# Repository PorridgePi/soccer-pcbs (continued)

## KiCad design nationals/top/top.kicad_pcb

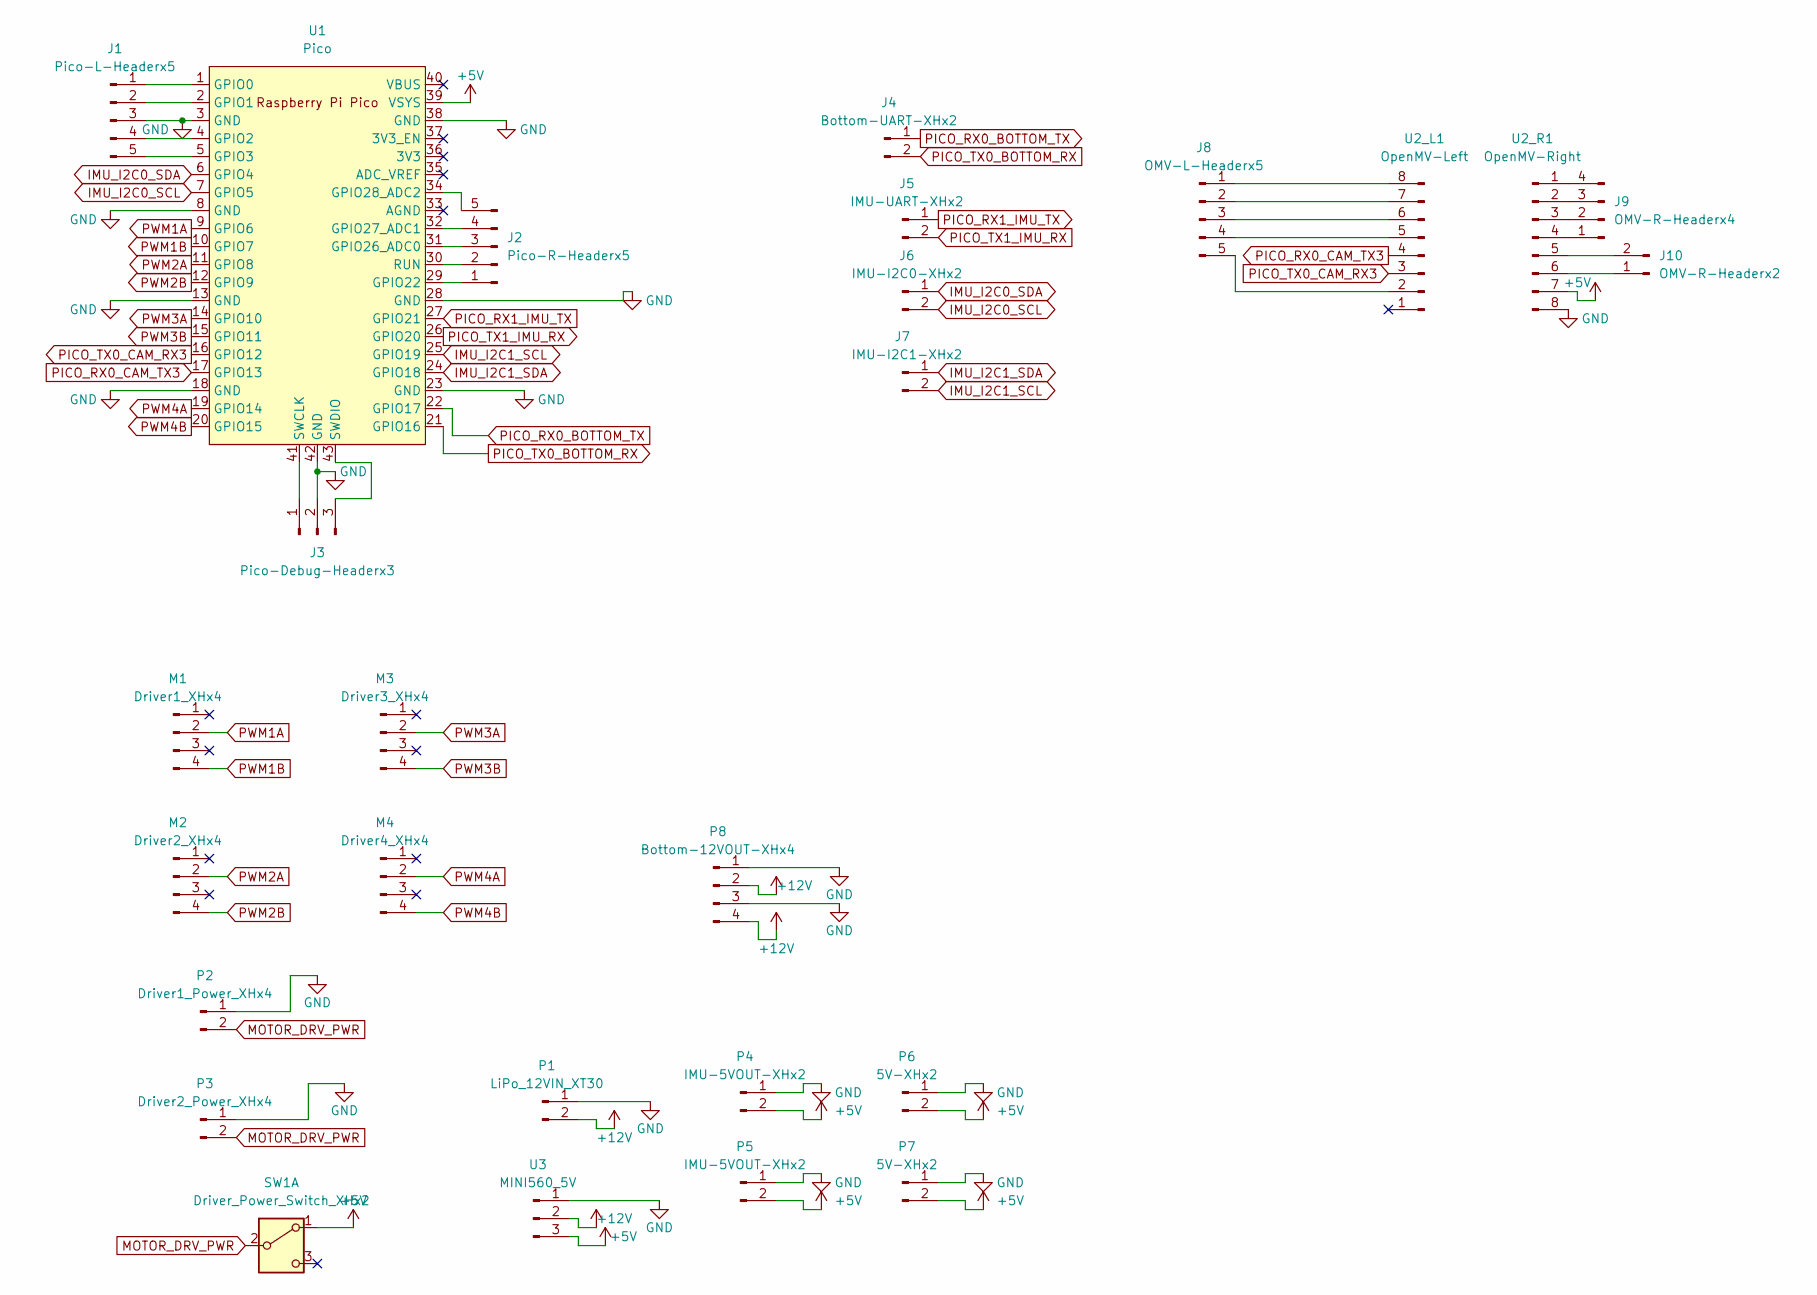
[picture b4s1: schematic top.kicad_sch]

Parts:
J1: Pico-L-Headerx5; PinHeader_1x05_P2.54mm_Vertical
J2: Pico-R-Headerx5; PinHeader_1x05_P2.54mm_Vertical
J3: Pico-Debug-Headerx3; PinHeader_1x03_P2.54mm_Vertical
J4: Bottom-UART-XHx2; JST_XH_B2B-XH-A_1x02_P2.50mm_Vertical
J5: IMU-UART-XHx2; JST_XH_B2B-XH-A_1x02_P2.50mm_Vertical
J6: IMU-I2C0-XHx2; JST_XH_B2B-XH-A_1x02_P2.50mm_Vertical
J7: IMU-I2C1-XHx2; JST_XH_B2B-XH-A_1x02_P2.50mm_Vertical
J8: OMV-L-Headerx5; PinHeader_1x05_P2.54mm_Vertical
J9: OMV-R-Headerx4; PinSocket_1x04_P2.54mm_Vertical
J10: OMV-R-Headerx2; PinHeader_1x02_P2.54mm_Vertical
M1: Driver1_XHx4; JST_XH_B4B-XH-A_1x04_P2.50mm_Vertical
M2: Driver2_XHx4; JST_XH_B4B-XH-A_1x04_P2.50mm_Vertical
M3: Driver3_XHx4; JST_XH_B4B-XH-A_1x04_P2.50mm_Vertical
M4: Driver4_XHx4; JST_XH_B4B-XH-A_1x04_P2.50mm_Vertical
P1: LiPo_12VIN_XT30; AMASS_XT30PW-F_1x02_P2.50mm_Horizontal
P2: Driver1_Power_XHx4; JST_XH_B2B-XH-A_1x02_P2.50mm_Vertical
P3: Driver2_Power_XHx4; JST_XH_B2B-XH-A_1x02_P2.50mm_Vertical
P4, P5: IMU-5VOUT-XHx2; JST_XH_B2B-XH-A_1x02_P2.50mm_Vertical
P6, P7: 5V-XHx2; JST_XH_B2B-XH-A_1x02_P2.50mm_Vertical
P8: Bottom-12VOUT-XHx4; JST_XH_B4B-XH-A_1x04_P2.50mm_Vertical
SW1: Driver_Power_Switch_XHx2; JST_XH_B2B-XH-A_1x02_P2.50mm_Vertical
U1: Pico; Raspberry_Pi_Pico_SMT_THT
U2_L1: OpenMV-Left; PinHeader_1x08_P2.54mm_Vertical
U2_R1: OpenMV-Right; PinHeader_1x08_P2.54mm_Vertical
U3: MINI560_5V; MINI560

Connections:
+5V: P4.2, P5.2, P6.2, P7.2, SW1.1 (A), U1.39 (VSYS), U2_R1.7, U3.3
+12V: P1.2, P8.2, P8.4, U3.2
GND: J1.3, J3.2, P1.1, P2.1, P3.1, P4.1, P5.1, P6.1, P7.1, P8.1, P8.3, U1.3 (GND), U1.8 (GND), U1.13 (GND), U1.18 (GND), U1.23 (GND), U1.28 (GND), U1.38 (GND), U1.42 (GND), U2_R1.8, U3.1
IMU_I2C0_SCL: J6.2, U1.7 (GPIO5)
IMU_I2C0_SDA: J6.1, U1.6 (GPIO4)
IMU_I2C1_SCL: J7.2, U1.25 (GPIO19)
IMU_I2C1_SDA: J7.1, U1.24 (GPIO18)
MOTOR_DRV_PWR: P2.2, P3.2, SW1.2 (B)
unnamed: J1.1, U1.1 (GPIO0)
unnamed: J1.2, U1.2 (GPIO1)
unnamed: J1.4, U1.4 (GPIO2)
unnamed: J1.5, U1.5 (GPIO3)
unnamed: J2.1, U1.29 (GPIO22)
unnamed: J2.2, U1.30 (RUN)
unnamed: J2.3, U1.31 (GPIO26_ADC0)
unnamed: J2.4, U1.32 (GPIO27_ADC1)
unnamed: J2.5, U1.34 (GPIO28_ADC2)
unnamed: J3.1, U1.41 (SWCLK)
unnamed: J3.3, U1.43 (SWDIO)
unnamed: J8.1, U2_L1.8
unnamed: J8.2, U2_L1.7
unnamed: J8.3, U2_L1.6
unnamed: J8.4, U2_L1.5
unnamed: J8.5, U2_L1.2
unnamed: J9.1, U2_R1.4
unnamed: J9.2, U2_R1.3
unnamed: J9.3, U2_R1.2
unnamed: J9.4, U2_R1.1
unnamed: J10.1, U2_R1.6
unnamed: J10.2, U2_R1.5
PICO_RX0_BOTTOM_TX: J4.1, U1.22 (GPIO17)
PICO_RX0_CAM_TX3: U1.17 (GPIO13), U2_L1.4
PICO_RX1_IMU_TX: J5.1, U1.27 (GPIO21)
PICO_TX0_BOTTOM_RX: J4.2, U1.21 (GPIO16)
PICO_TX0_CAM_RX3: U1.16 (GPIO12), U2_L1.3
PICO_TX1_IMU_RX: J5.2, U1.26 (GPIO20)
PWM1A: M1.2, U1.9 (GPIO6)
PWM1B: M1.4, U1.10 (GPIO7)
PWM2A: M2.2, U1.11 (GPIO8)
PWM2B: M2.4, U1.12 (GPIO9)
PWM3A: M3.2, U1.14 (GPIO10)
PWM3B: M3.4, U1.15 (GPIO11)
PWM4A: M4.2, U1.19 (GPIO14)
PWM4B: M4.4, U1.20 (GPIO15)

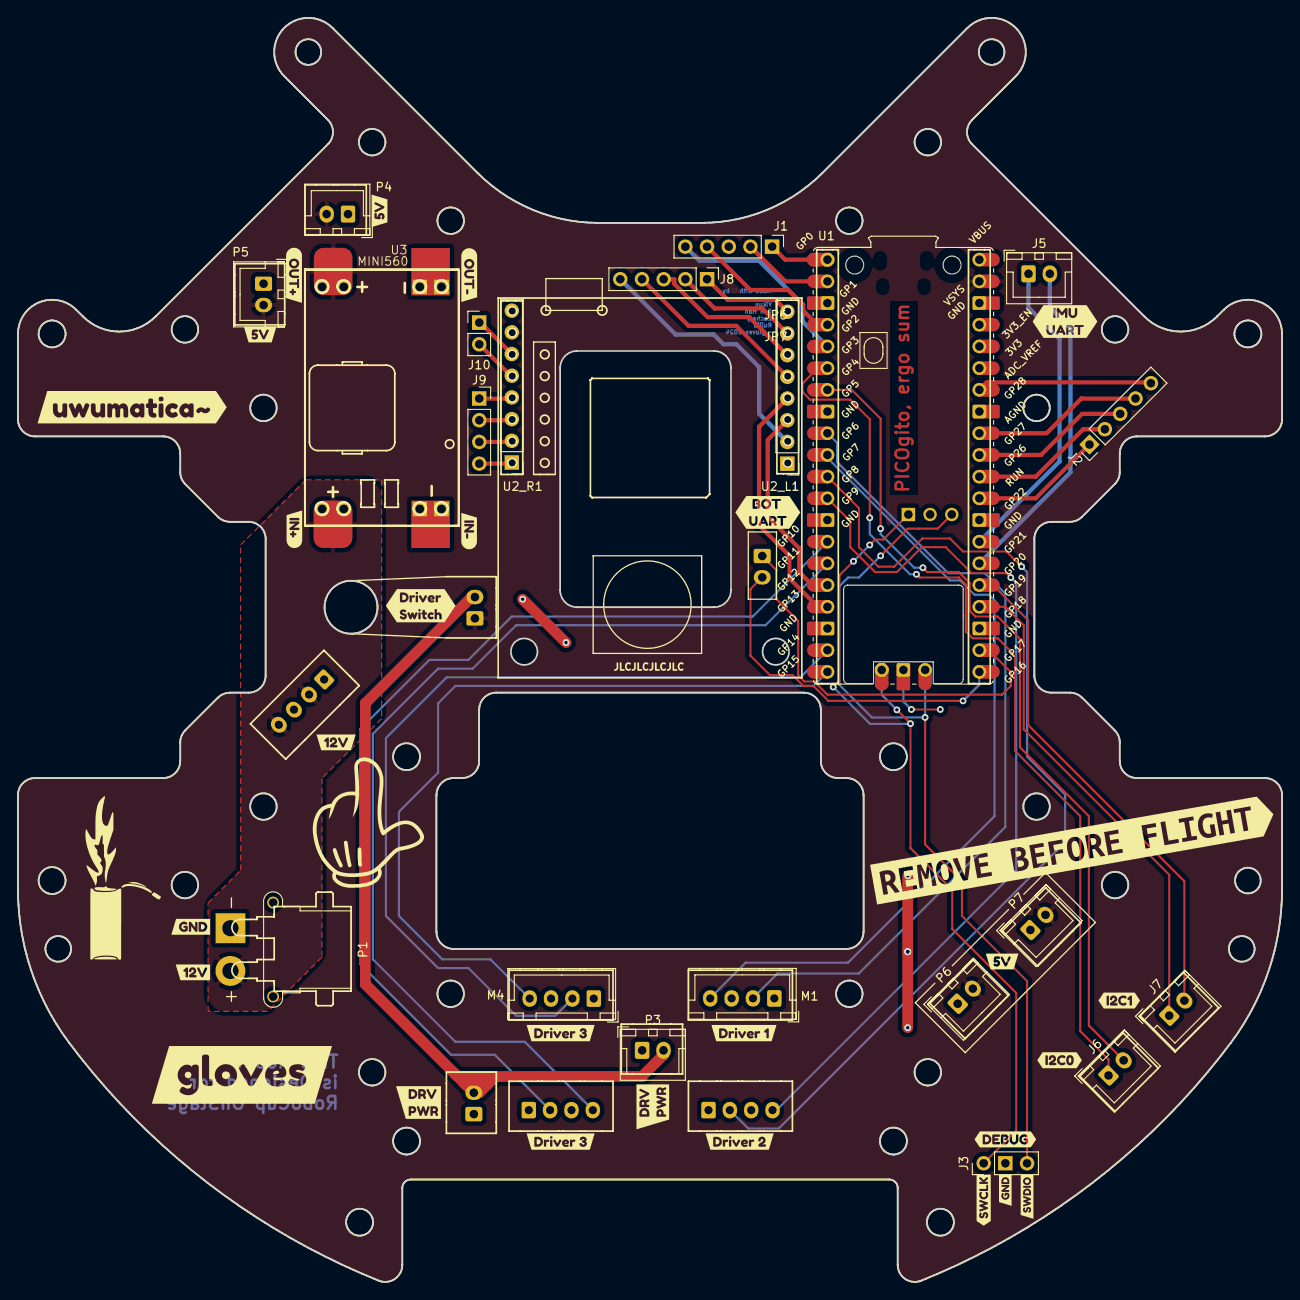
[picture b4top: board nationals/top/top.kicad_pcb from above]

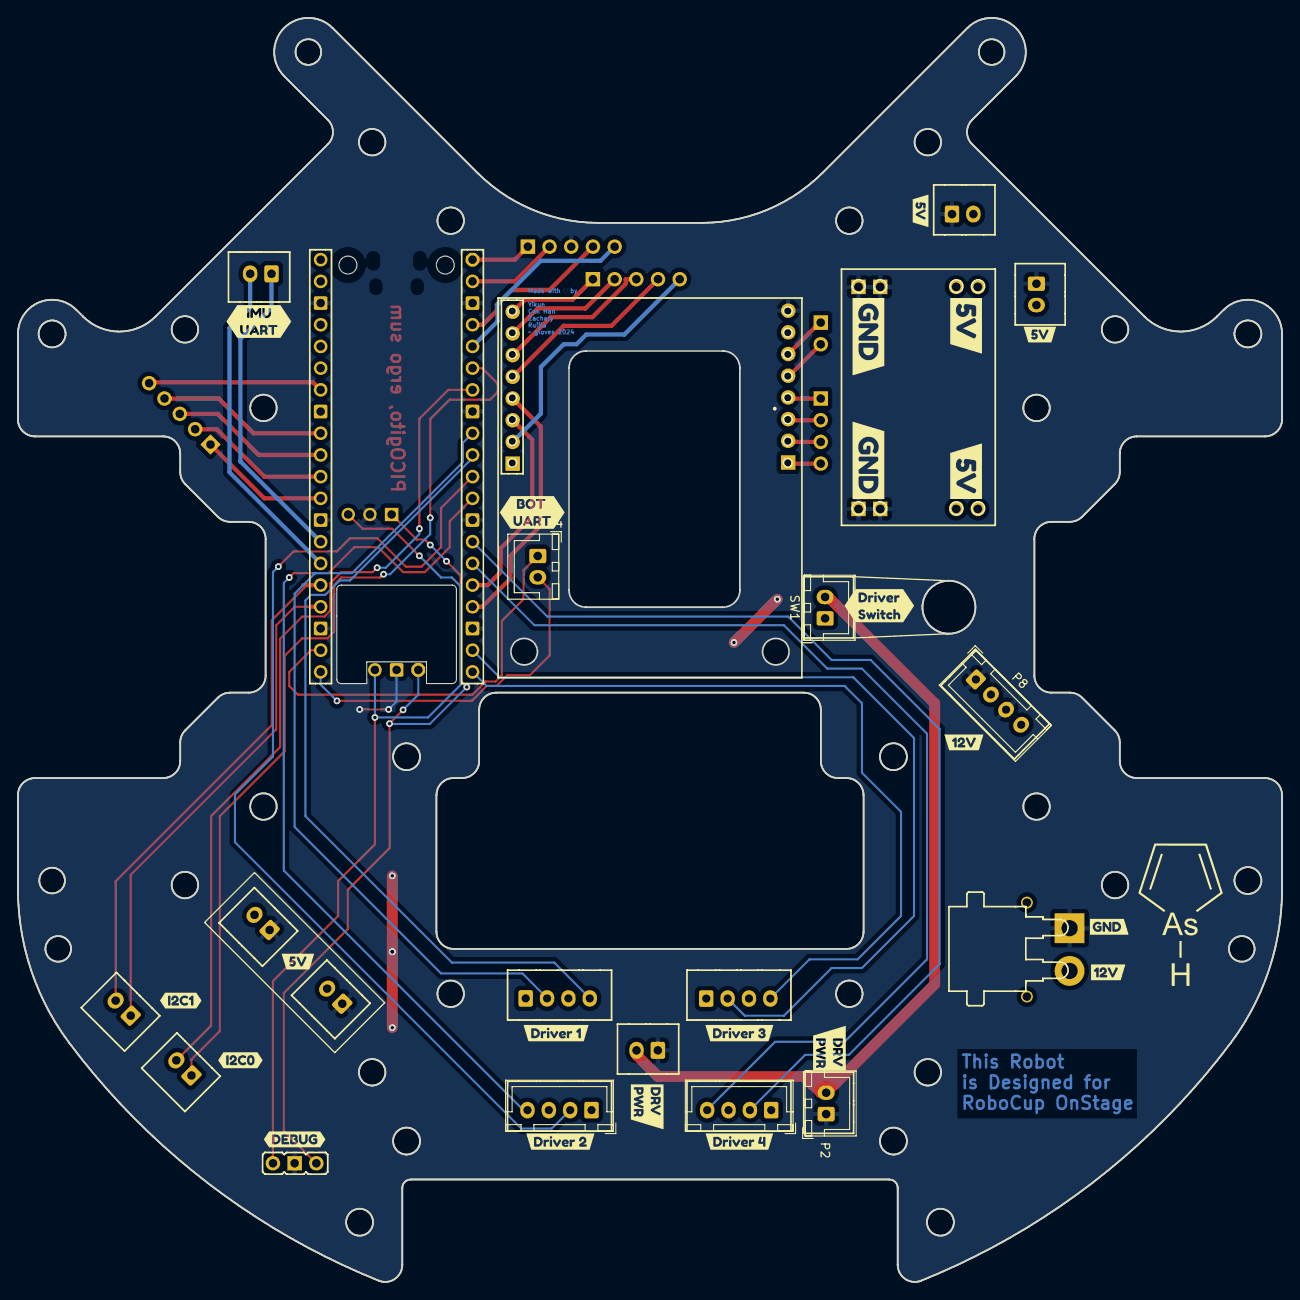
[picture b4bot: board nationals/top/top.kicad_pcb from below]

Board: 2 copper layers, 148.0 x 148.0 mm, 73 parts (28 on the bottom side), 44 nets.

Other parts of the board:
kibuzzard-65B87A32, kibuzzard-65B87A32#2, kibuzzard-65B87A32#3, kibuzzard-65B87A32#4, kibuzzard-65B87A32#5, kibuzzard-65B87A32#6: G***; kibuzzard-65B87A32
kibuzzard-65B87C2D: G***; kibuzzard-65B87C2D
kibuzzard-65B87C4C: G***; kibuzzard-65B87C4C
kibuzzard-65B87C77: G***; kibuzzard-65B87C77
kibuzzard-65B87C82: G***; kibuzzard-65B87C82
kibuzzard-65B87CF7, kibuzzard-65B87CF7#2: G***; kibuzzard-65B87CF7
kibuzzard-65B87D10, kibuzzard-65B87D10#2: G***; kibuzzard-65B87D10
kibuzzard-65B89F23: G***; kibuzzard-65B89F23
kibuzzard-65B872C5, kibuzzard-65B872C5#2, kibuzzard-65B872C5#3: G***; kibuzzard-65B872C5
kibuzzard-65B872D0: G***; kibuzzard-65B872D0
kibuzzard-65B874B6, kibuzzard-65B874B6#2: G***; kibuzzard-65B874B6
kibuzzard-65B876C6: G***; kibuzzard-65B876C6
kibuzzard-65B877B7, kibuzzard-65B877B7#2, kibuzzard-65B877B7#3: G***; kibuzzard-65B877B7
kibuzzard-65B878F9, kibuzzard-65B878F9#2: G***; kibuzzard-65B878F9
kibuzzard-65B8729F, kibuzzard-65B8729F#2: G***; kibuzzard-65B8729F
kibuzzard-65B8733B, kibuzzard-65B8733B#2: G***; kibuzzard-65B8733B
kibuzzard-65B8746C: G***; kibuzzard-65B8746C
kibuzzard-65B8747C: G***; kibuzzard-65B8747C
kibuzzard-65B8749D: G***; kibuzzard-65B8749D
kibuzzard-65B8779B: G***; kibuzzard-65B8779B
kibuzzard-65B8902F: G***; kibuzzard-65B8902F
kibuzzard-65B87292, kibuzzard-65B87292#2: G***; kibuzzard-65B87292
kibuzzard-65B87357, kibuzzard-65B87357#2: G***; kibuzzard-65B87357
kibuzzard-65B87709: G***; kibuzzard-65B87709
kibuzzard-65B87723: G***; kibuzzard-65B87723
kibuzzard-65B87731: G***; kibuzzard-65B87731
kibuzzard-65B87948, kibuzzard-65B87948#2: G***; kibuzzard-65B87948
kibuzzard-65B89082: G***; kibuzzard-65B89082

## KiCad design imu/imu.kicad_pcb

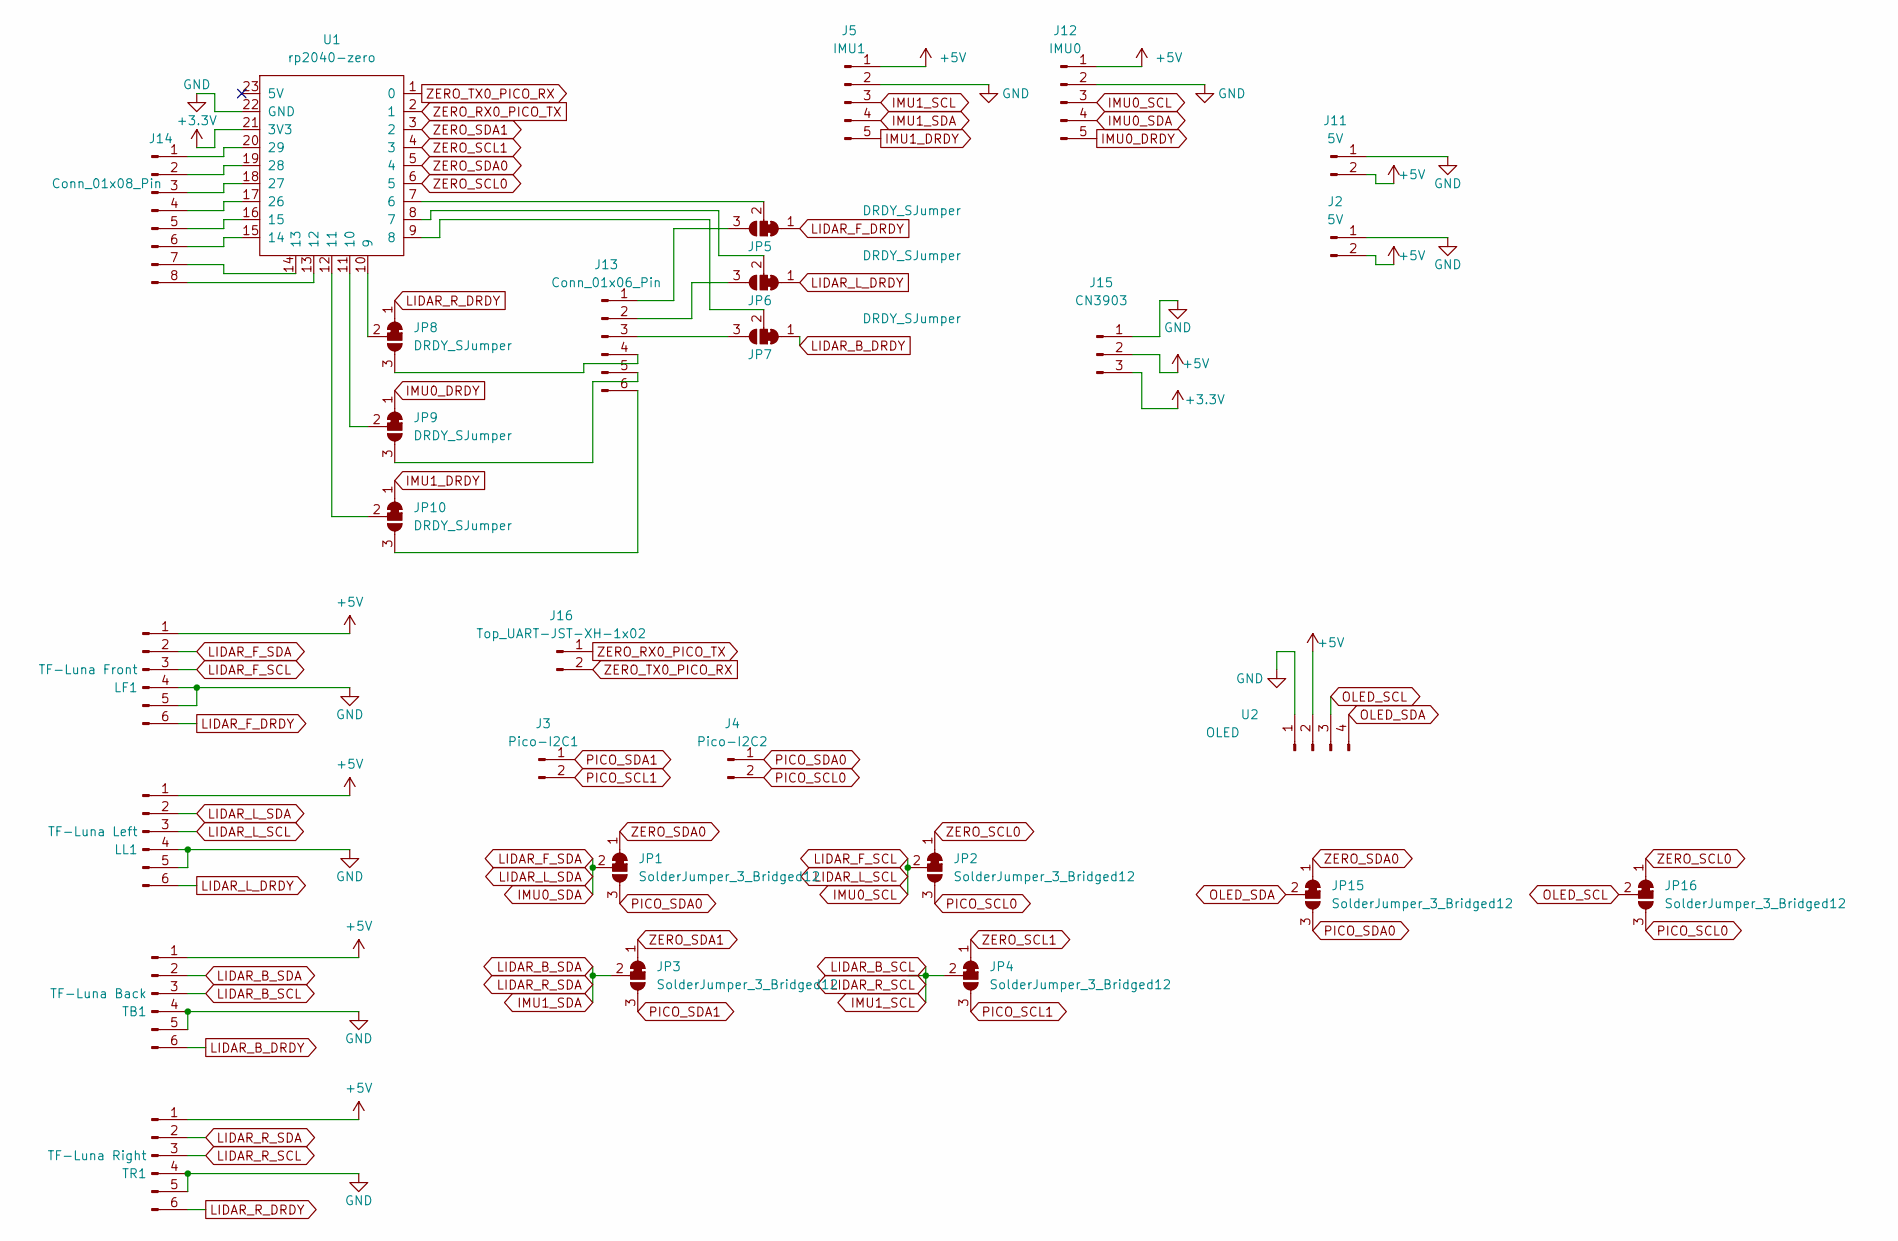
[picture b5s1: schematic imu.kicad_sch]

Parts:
J2, J11: 5V; JST_XH_B2B-XH-A_1x02_P2.50mm_Vertical
J3: Pico-I2C1; JST_XH_B2B-XH-A_1x02_P2.50mm_Vertical
J4: Pico-I2C2; JST_XH_B2B-XH-A_1x02_P2.50mm_Vertical
J5: IMU1; JST_XH_B5B-XH-A_1x05_P2.50mm_Vertical
J12: IMU0; JST_XH_B5B-XH-A_1x05_P2.50mm_Vertical
J13: Conn_01x06_Pin; PinHeader_1x06_P2.54mm_Vertical
J14: Conn_01x08_Pin; PinHeader_1x08_P2.54mm_Vertical
J15: CN3903
J16: Top_UART-JST-XH-1x02; JST_XH_B2B-XH-A_1x02_P2.50mm_Vertical
JP1, JP2, JP3, JP4, JP15, JP16: SolderJumper_3_Bridged12; SolderJumper-3_P1.3mm_Bridged2Bar12_RoundedPad1.0x1.5mm_Num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
JP5, JP6, JP7, JP8, JP9, JP10: DRDY_SJumper; SolderJumper-3_P1.3mm_Bridged2Bar12_RoundedPad1.0x1.5mm_Num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
LF1: TF-Luna Front; JST_XH_B6B-XH-A_1x06_P2.50mm_Vertical
LL1: TF-Luna Left; JST_XH_B6B-XH-A_1x06_P2.50mm_Vertical
TB1: TF-Luna Back; JST_XH_B6B-XH-A_1x06_P2.50mm_Vertical
TR1: TF-Luna Right; JST_XH_B6B-XH-A_1x06_P2.50mm_Vertical
U1: rp2040-zero; rp2040-zero-tht-pads
U2: OLED; PinHeader_1x04_P2.54mm_Vertical

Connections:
+3.3V: J15.3, U1.21 (3V3)
+5V: J2.2, J5.1, J11.2, J12.1, J15.2, LF1.1, LL1.1, TB1.1, TR1.1, U2.2
GND: J2.1, J5.2, J11.1, J12.2, J15.1, LF1.4, LF1.5, LL1.4, LL1.5, TB1.4, TB1.5, TR1.4, TR1.5, U1.22 (GND), U2.1
IMU0_DRDY: J12.5, JP9.1 (A)
IMU0_SCL: J12.3, JP2.2 (C), LF1.3, LL1.3
IMU0_SDA: J12.4, JP1.2 (C), LF1.2, LL1.2
IMU1_DRDY: J5.5, JP10.1 (A)
IMU1_SCL: J5.3, JP4.2 (C), TB1.3, TR1.3
IMU1_SDA: J5.4, JP3.2 (C), TB1.2, TR1.2
LIDAR_B_DRDY: JP7.1 (A), TB1.6
LIDAR_F_DRDY: JP5.1 (A), LF1.6
LIDAR_L_DRDY: JP6.1 (A), LL1.6
LIDAR_R_DRDY: JP8.1 (A), TR1.6
unnamed: J13.1, JP5.3 (B)
unnamed: J13.2, JP6.3 (B)
unnamed: J13.3, JP7.3 (B)
unnamed: J13.4, JP8.3 (B)
unnamed: J13.5, JP9.3 (B)
unnamed: J13.6, JP10.3 (B)
unnamed: J14.1, U1.20 (29)
unnamed: J14.2, U1.19 (28)
unnamed: J14.3, U1.18 (27)
unnamed: J14.4, U1.17 (26)
unnamed: J14.5, U1.16 (15)
unnamed: J14.6, U1.15 (14)
unnamed: J14.7, U1.14 (13)
unnamed: J14.8, U1.13 (12)
unnamed: JP5.2 (C), U1.7 (6)
unnamed: JP6.2 (C), U1.8 (7)
unnamed: JP7.2 (C), U1.9 (8)
unnamed: JP8.2 (C), U1.10 (9)
unnamed: JP9.2 (C), U1.11 (10)
unnamed: JP10.2 (C), U1.12 (11)
OLED_SCL: JP16.2 (C), U2.3
OLED_SDA: JP15.2 (C), U2.4
PICO_SCL0: J4.2, JP2.3 (B), JP16.3 (B)
PICO_SCL1: J3.2, JP4.3 (B)
PICO_SDA0: J4.1, JP1.3 (B), JP15.3 (B)
PICO_SDA1: J3.1, JP3.3 (B)
ZERO_RX0_PICO_TX: J16.1, U1.2 (1)
ZERO_SCL0: JP2.1 (A), JP16.1 (A), U1.6 (5)
ZERO_SCL1: JP4.1 (A), U1.4 (3)
ZERO_SDA0: JP1.1 (A), JP15.1 (A), U1.5 (4)
ZERO_SDA1: JP3.1 (A), U1.3 (2)
ZERO_TX0_PICO_RX: J16.2, U1.1 (0)

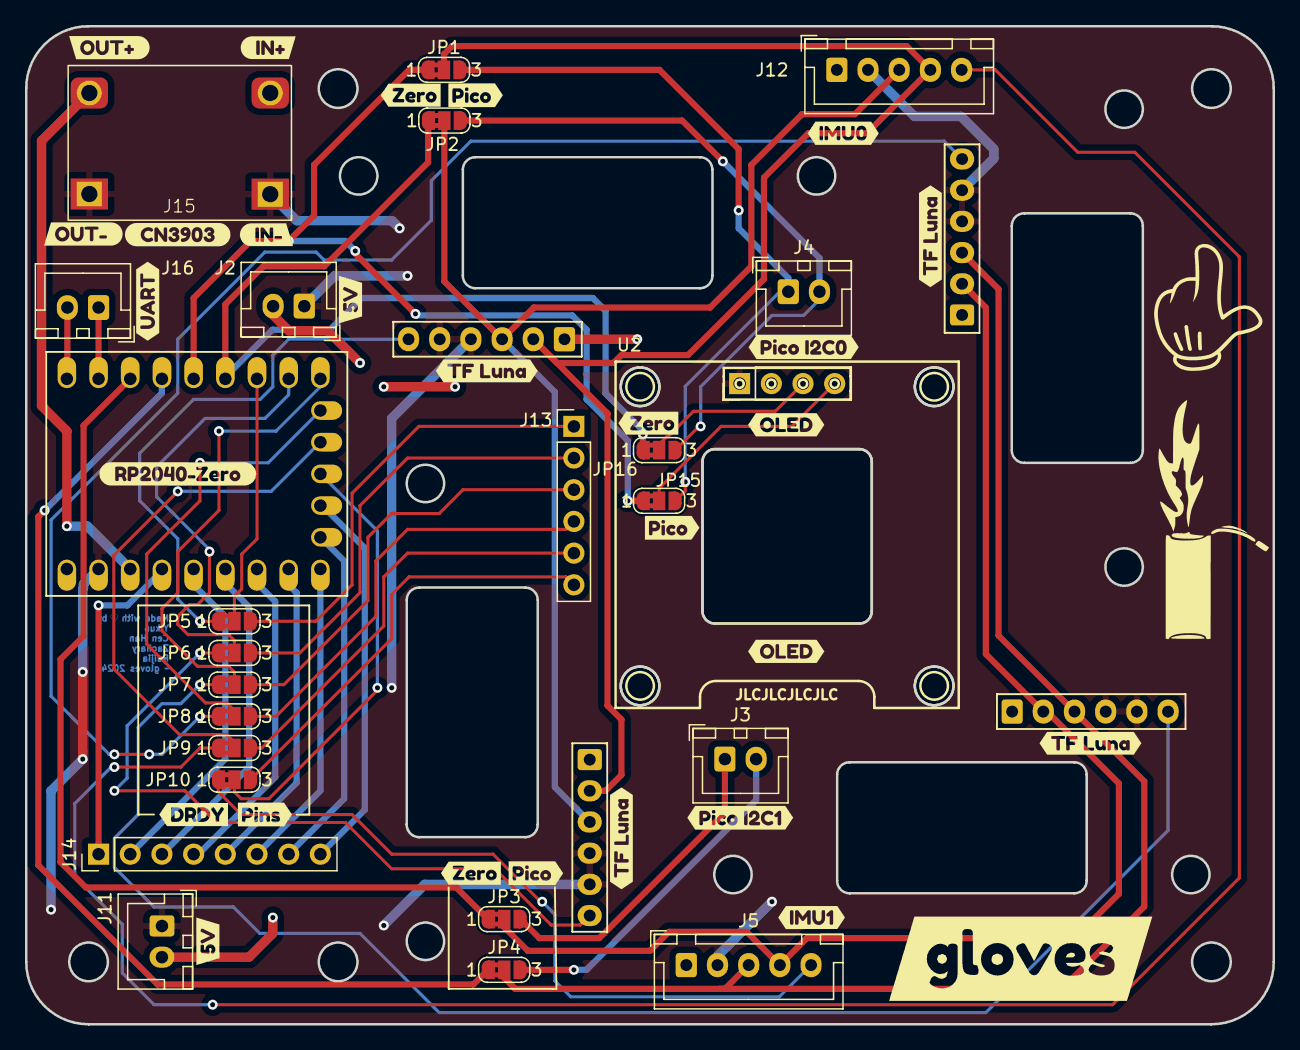
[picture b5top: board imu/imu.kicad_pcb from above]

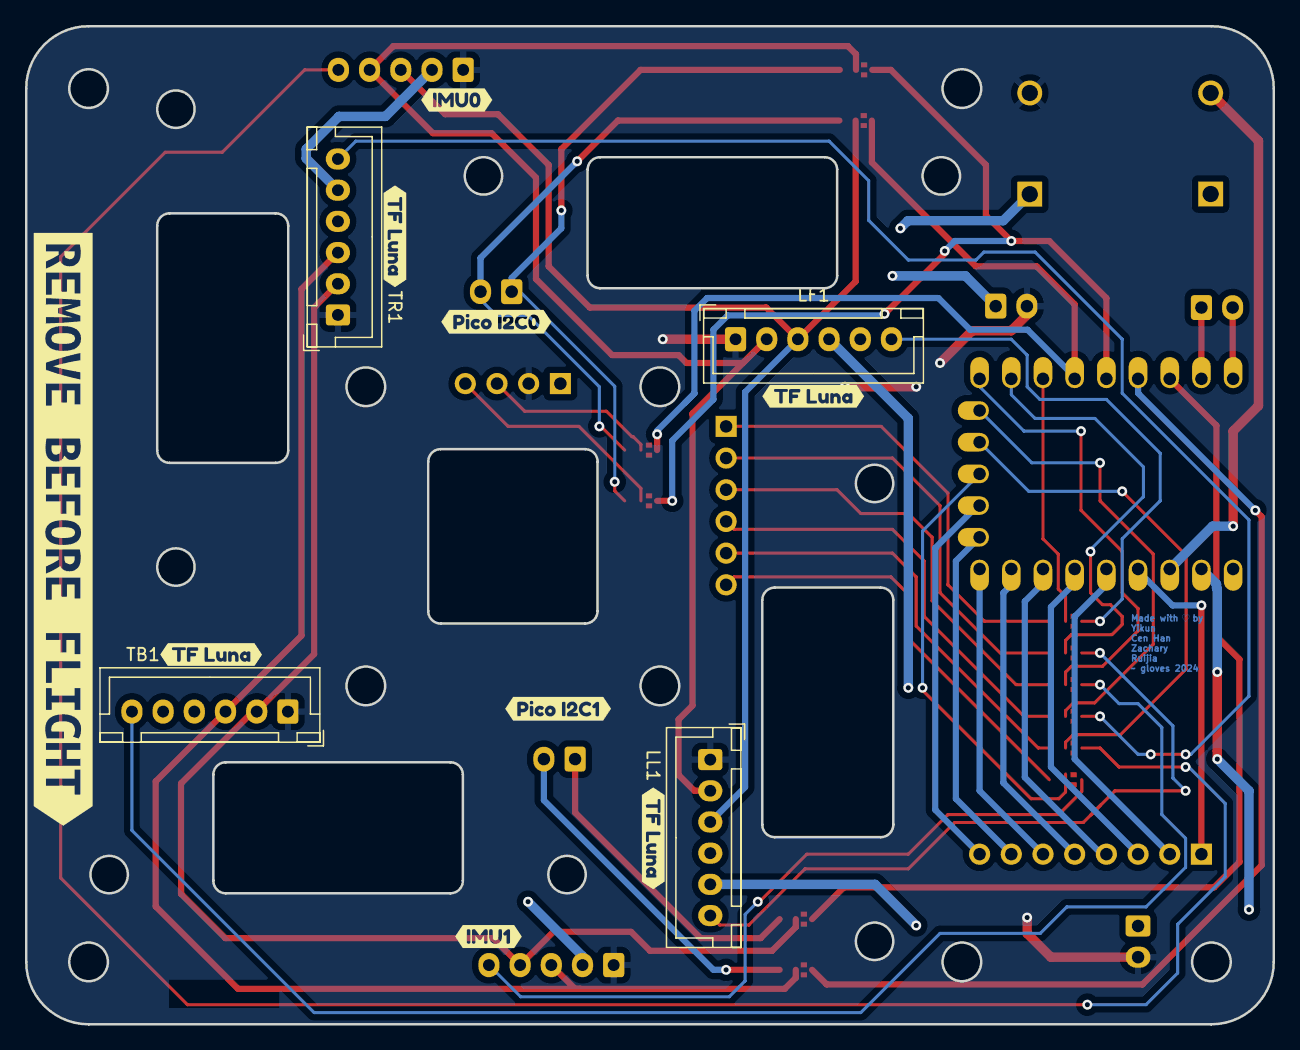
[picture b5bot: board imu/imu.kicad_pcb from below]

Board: 2 copper layers, 100.0 x 80.0 mm, 60 parts (13 on the bottom side), 45 nets.

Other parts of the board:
kibuzzard-65B8A084: G***; kibuzzard-65B8A084
kibuzzard-65B88A9E, kibuzzard-65B88A9E#2: G***; kibuzzard-65B88A9E
kibuzzard-65B88A19: G***; kibuzzard-65B88A19
kibuzzard-65B88A26: G***; kibuzzard-65B88A26
kibuzzard-65B88AB7, kibuzzard-65B88AB7#2: G***; kibuzzard-65B88AB7
kibuzzard-65B88AD7: G***; kibuzzard-65B88AD7
kibuzzard-65B88B43: G***; kibuzzard-65B88B43
kibuzzard-65B88B83, kibuzzard-65B88B83#2: G***; kibuzzard-65B88B83
kibuzzard-65B88C0A, kibuzzard-65B88C0A#2, kibuzzard-65B88C0A#3: G***; kibuzzard-65B88C0A
kibuzzard-65B88C1A, kibuzzard-65B88C1A#2, kibuzzard-65B88C1A#3: G***; kibuzzard-65B88C1A
kibuzzard-65B88CBD, kibuzzard-65B88CBD#2: G***; kibuzzard-65B88CBD
kibuzzard-65B88CCD, kibuzzard-65B88CCD#2: G***; kibuzzard-65B88CCD
kibuzzard-65B88D4B, kibuzzard-65B88D4B#2, kibuzzard-65B88D4B#3, kibuzzard-65B88D4B#4, kibuzzard-65B88D4B#5, kibuzzard-65B88D4B#6, kibuzzard-65B88D4B#7, kibuzzard-65B88D4B#8: G***; kibuzzard-65B88D4B
kibuzzard-65B88E1E, kibuzzard-65B88E1E#2: G***; kibuzzard-65B88E1E
kibuzzard-65B88EA6: G***; kibuzzard-65B88EA6

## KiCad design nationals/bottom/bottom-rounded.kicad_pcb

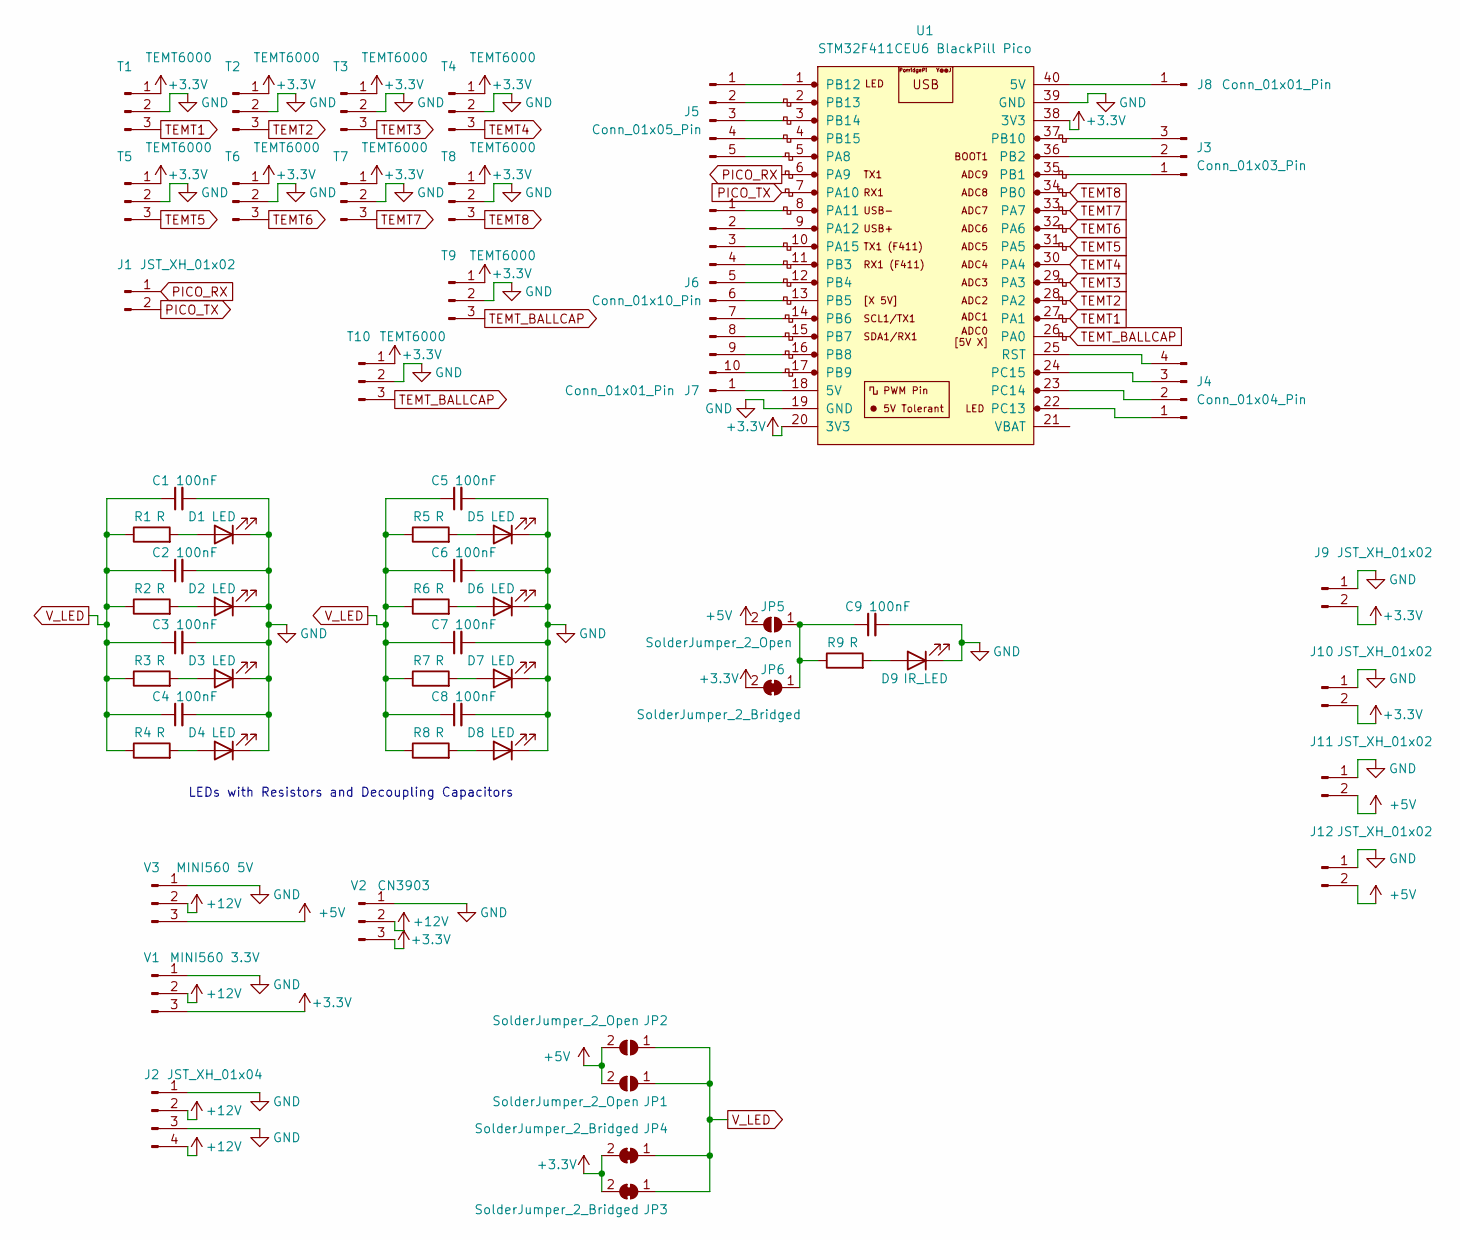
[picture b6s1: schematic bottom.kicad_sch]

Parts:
C1, C2, C3, C4, C5, C6, C7, C8, C9: 100nF; C_0201_0603Metric_Pad0.64x0.40mm_HandSolder
D1, D2, D3, D4, D5, D6, D7, D8: LED; LED-6028
D9: IR_LED; LED_D5.0mm_Horizontal_O1.27mm_Z3.0mm
J1, J9, J10, J11, J12: JST_XH_01x02; JST_XH_B2B-XH-A_1x02_P2.50mm_Vertical
J2: JST_XH_01x04; JST_XH_B4B-XH-A_1x04_P2.50mm_Vertical
J3: Conn_01x03_Pin; PinHeader_1x03_P2.54mm_Vertical
J4: Conn_01x04_Pin; PinHeader_1x04_P2.54mm_Vertical
J5: Conn_01x05_Pin; PinHeader_1x05_P2.54mm_Vertical
J6: Conn_01x10_Pin; PinHeader_1x10_P2.54mm_Vertical
J7, J8: Conn_01x01_Pin; PinHeader_1x01_P2.54mm_Vertical
JP1, JP2, JP5: SolderJumper_2_Open; SolderJumper-2_P1.3mm_Open_RoundedPad1.0x1.5mm
JP3, JP4, JP6: SolderJumper_2_Bridged; SolderJumper-2_P1.3mm_Bridged2Bar_RoundedPad1.0x1.5mm
R1, R2, R3, R4, R5, R6, R7, R8, R9: R; R_0201_0603Metric_Pad0.64x0.40mm_HandSolder
T1, T2, T3, T4, T5, T6, T7, T8: TEMT6000
T9: TEMT6000; TEMT6000-ballcap
T10: TEMT6000; TEMT6000-wire
U1: STM32F411CEU6 BlackPill Pico; STM32FE411CEU6_Pico_SMD_TH
V1: MINI560 3.3V; MINI560
V2: CN3903
V3: MINI560 5V; MINI560

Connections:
+3.3V: J9.2, J10.2, JP3.2 (B), JP4.2 (B), JP6.2 (B), T1.1, T2.1, T3.1, T4.1, T5.1, T6.1, T7.1, T8.1, T9.1, T10.1, U1.20 (3V3), U1.38 (3V3), V1.3, V2.3
+5V: J11.2, J12.2, JP1.2 (B), JP2.2 (B), JP5.2 (B), V3.3
+12V: J2.2, J2.4, V1.2, V2.2, V3.2
GND: C1.2, C2.2, C3.2, C4.2, C5.2, C6.2, C7.2, C8.2, C9.2, D1.1 (K), D2.1 (K), D3.1 (K), D4.1 (K), D5.1 (K), D6.1 (K), D7.1 (K), D8.1 (K), D9.1 (K), J2.1, J2.3, J9.1, J10.1, J11.1, J12.1, T1.2, T2.2, T3.2, T4.2, T5.2, T6.2, T7.2, T8.2, T9.2, T10.2, U1.19 (GND), U1.39 (GND), V1.1, V2.1, V3.1
unnamed: D1.2 (A), R1.2
unnamed: D2.2 (A), R2.2
unnamed: D3.2 (A), R3.2
unnamed: D4.2 (A), R4.2
unnamed: D5.2 (A), R5.2
unnamed: D6.2 (A), R6.2
unnamed: D7.2 (A), R7.2
unnamed: D8.2 (A), R8.2
unnamed: D9.2 (A), R9.2
unnamed: J3.1, U1.35 (PB1)
unnamed: J3.2, U1.36 (PB2)
unnamed: J3.3, U1.37 (PB10)
unnamed: J4.1, U1.22 (PC13)
unnamed: J4.2, U1.23 (PC14)
unnamed: J4.3, U1.24 (PC15)
unnamed: J4.4, U1.25 (RST)
unnamed: J5.1, U1.1 (PB12)
unnamed: J5.2, U1.2 (PB13)
unnamed: J5.3, U1.3 (PB14)
unnamed: J5.4, U1.4 (PB15)
unnamed: J5.5, U1.5 (PA8)
unnamed: J6.1, U1.8 (PA11)
unnamed: J6.2, U1.9 (PA12)
unnamed: J6.3, U1.10 (PA15)
unnamed: J6.4, U1.11 (PB3)
unnamed: J6.5, U1.12 (PB4)
unnamed: J6.6, U1.13 (PB5)
unnamed: J6.7, U1.14 (PB6)
unnamed: J6.8, U1.15 (PB7)
unnamed: J6.9, U1.16 (PB8)
unnamed: J6.10, U1.17 (PB9)
unnamed: J7.1, U1.18 (5V)
unnamed: J8.1, U1.40 (5V)
unnamed: C9.1, JP5.1 (A), JP6.1 (A), R9.1
PICO_RX: J1.1, U1.6 (PA9)
PICO_TX: J1.2, U1.7 (PA10)
TEMT1: T1.3, U1.27 (PA1)
TEMT2: T2.3, U1.28 (PA2)
TEMT3: T3.3, U1.29 (PA3)
TEMT4: T4.3, U1.30 (PA4)
TEMT5: T5.3, U1.31 (PA5)
TEMT6: T6.3, U1.32 (PA6)
TEMT7: T7.3, U1.33 (PA7)
TEMT8: T8.3, U1.34 (PB0)
TEMT_BALLCAP: T9.3, T10.3, U1.26 (PA0)
V_LED: C1.1, C2.1, C3.1, C4.1, C5.1, C6.1, C7.1, C8.1, JP1.1 (A), JP2.1 (A), JP3.1 (A), JP4.1 (A), R1.1, R2.1, R3.1, R4.1, R5.1, R6.1, R7.1, R8.1

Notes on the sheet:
LEDs with Resistors and Decoupling Capacitors
